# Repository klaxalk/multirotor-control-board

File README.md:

Multirotor Control Board
========================

Sources for the Multirotor Control Board developed at FEE CTU Prague by MRS Group. There are software and hardware sources located in this repository.

The control board is responsible for communication with modules and running basic controller for stabilization and surveilence.

------
### References
1. T. Baca, "_[Embedded Model Predictive Control of Unmanned Micro Aerial Vehicles](http://mrs.felk.cvut.cz/data/papers/DP_baca.pdf)_", 2015, Diploma Thesis, Czech Technical University in Prague.
2. T. Baca, G. Loianno and M. Saska, "_[Embedded Model Predictive Control of Unmanned Micro Aerial Vehicles](http://mrs.felk.cvut.cz/data/papers/mmar_2018_mpc.pdf)_". In 2016 21st International Conference on Methods and Models in Automation and Robotics (MMAR), 2016.
3. T. Baca, D. Hert, G. Loianno, M. Saska and V. Kumar, "_[Model Predictive Trajectory Tracking and Collision Avoidance for Reliable Outdoor Deployment of Unmanned Aerial Vehicles](http://mrs.felk.cvut.cz/data/papers/iros_2018_mpc.pdf)_". In IEEE International Conference on Intelligent Robots and Systems (IROS). 2018, 1-8.

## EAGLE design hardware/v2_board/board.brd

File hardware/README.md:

v1_board
--------

Eagle files for control board v1, January 2013.

v2_board
--------

Eagle files for control board v2, September 2014.

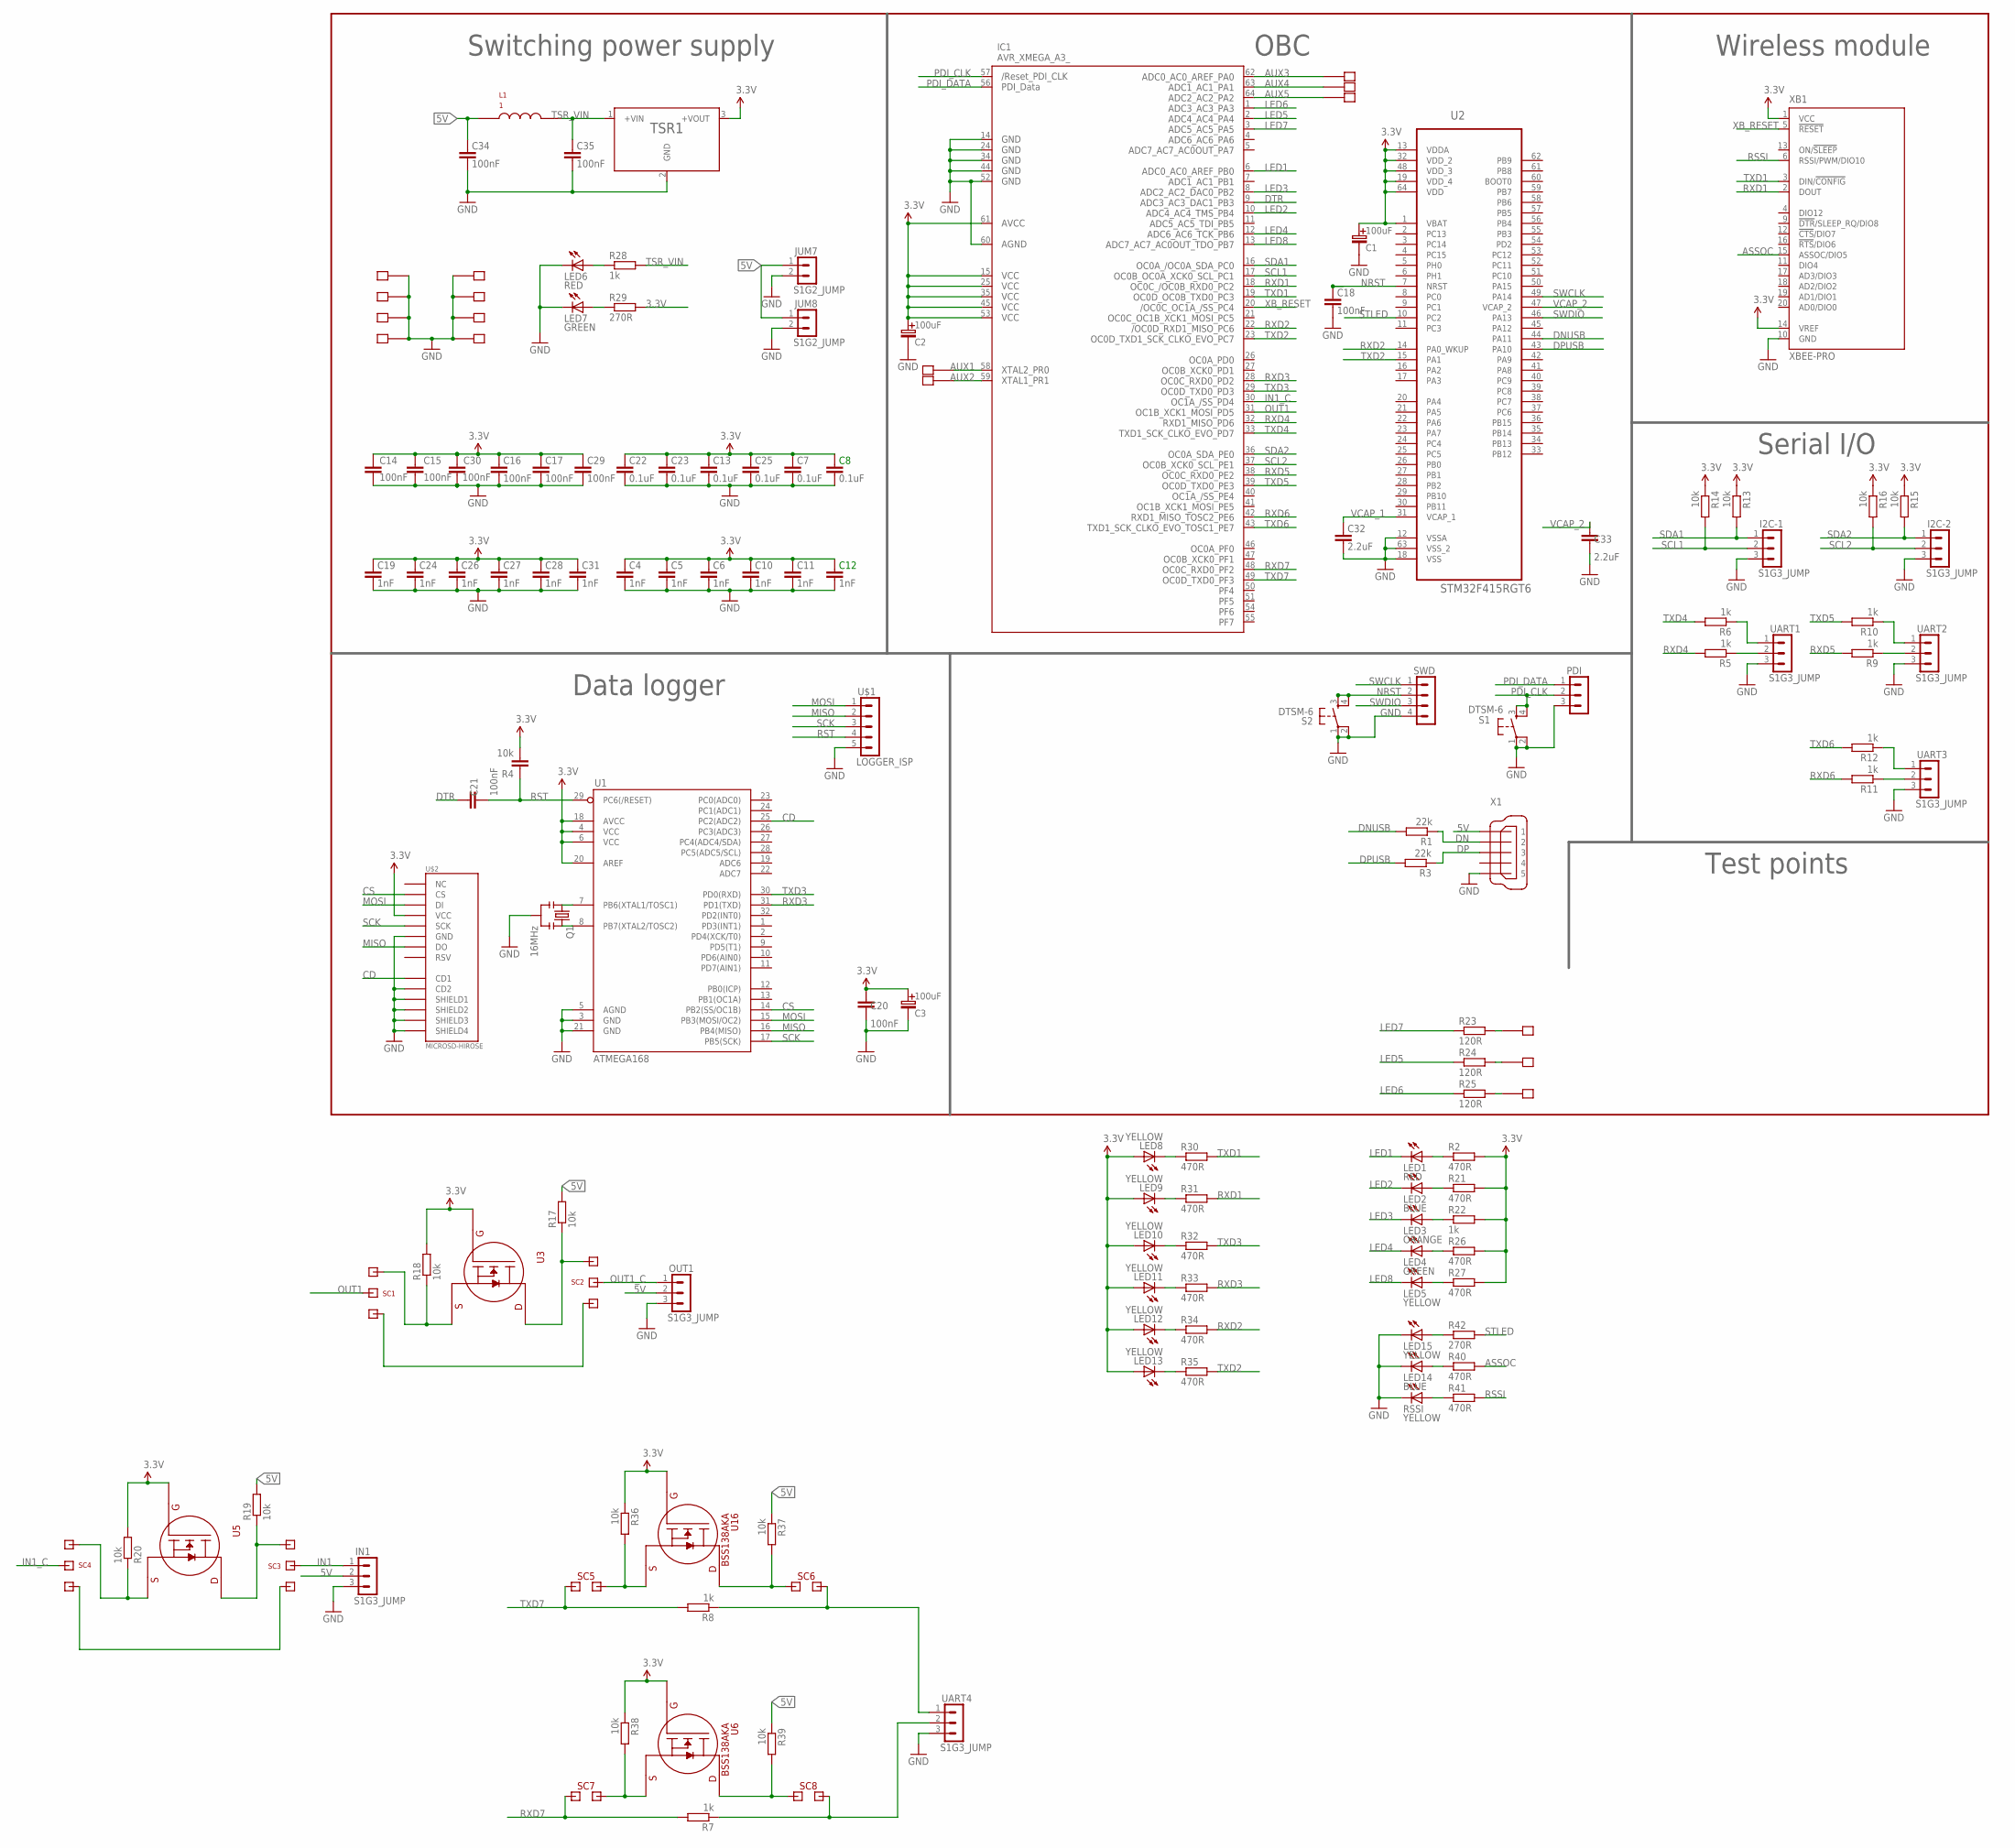
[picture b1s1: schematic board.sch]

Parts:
AUX1, AUX2, AUX3, AUX4, AUX5: PIN
C1, C2, C3: 100uF; B
C4, C5, C6, C10, C11, C12, C19, C24, C26, C27, C28, C31: 1nF; C0805
C7, C8, C13, C22, C23, C25: 0.1uF; C0805
C14, C15, C16, C17, C18, C20, C21, C29, C30, C34, C35: 100nF; C0805
C32, C33: 2.2uF; C0805
I2C-1, I2C-2: S1G3_JUMP; S1G3_JUM
IC1: AVR_XMEGA_A3_; TQFP64
IN1: S1G3_JUMP; S1G3_JUM
JUM7, JUM8: S1G2_JUMP; S1G2_JUM
L1: 1; SDR0604
LED1, LED6: RED; SML0805
LED2, LED14: BLUE; SML0805
LED3: ORANGE; SML0805
LED4, LED7: GREEN; SML0805
LED5, LED8, LED9, LED10, LED11, LED12, LED13, LED15: YELLOW; SML0805
OUT1: S1G3_JUMP; S1G3_JUM
PDI: S1G3_JUMP; S1G3_JUM
Q1: 16MHz; RESONATOR-SMD
R1, R3: 22k; R0805
R2, R21, R26, R27, R30, R31, R32, R33, R34, R35, R40, R41: 470R; R0805
R4: 10k; C0805
R5, R6, R7, R8, R9, R10, R11, R12, R22, R28: 1k; R0805
R13, R14, R15, R16, R17, R18, R19, R20, R36, R37, R38, R39: 10k; R0805
R23, R24, R25: 120R; R0805
R29, R42: 270R; R0805
RSSI: YELLOW; SML0805
S1, S2: DTSM-6
SC1, SC3: SOLDER_SWITCH_ONE; SOLDER_SWITCH
SC2, SC4: SOLDER_SWITCH_TWO; SOLDER_SWITCH
SC5, SC6, SC7, SC8: SOLDER_SWITCH_2
SWD: S1G4_JUMP_SQUARE; 2X02
TSR: TSR1
U1: ATMEGA168; TQFP32-08
U2: STM32F415RGT6; QFP50P1200X1200X160-64N
U3, U5, U6, U16: BSS138AKA; SOT-23
U$1: LOGGER_ISP
U$2: MICROSD-HIROSE; MICROSD_HOLDER-HIROSE-DM3AT
U$10, U$11, U$12, U$15, U$16, U$17, U$18, U$19, U$20, U$21, U$22: PIN
UART1, UART2, UART3, UART4: S1G3_JUMP; S1G3_JUM
X1: MINI-USB-UX60A-MB-5ST; UX60A-MB-5ST
XB1: XBEE-PRO

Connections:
3.3V: C1.+ (C_EL+), C2.+ (C_EL+), C3.+ (C_EL+), C4.2, C5.2, C6.2, C7.2, C8.2, C10.2, C11.2, C12.2, C13.2, C14.2, C15.2, C16.2, C17.2, C19.2, C20.2, C22.2, C23.2, C24.2, C25.2, C26.2, C27.2, C28.2, C29.2, C30.2, C31.2, IC1.15 (VCC1), IC1.25 (VCC2), IC1.35 (VCC3), IC1.45 (VCC4), IC1.53 (VCC5), IC1.61 (AVCC), LED8.A, LED9.A, LED10.A, LED11.A, LED12.A, LED13.A, R2.2, R4.2, R13.1, R14.1, R15.1, R16.1, R18.2, R20.2, R21.2, R22.2, R26.2, R27.2, R29.2, R36.1, R38.1, TSR.3 (+VOUT), U1.4 (VCC), U1.6 (VCC), U1.18 (AVCC), U1.20 (AREF), U2.1 (VBAT), U2.13 (VDDA), U2.19 (VDD_4), U2.32 (VDD_2), U2.48 (VDD_3), U2.64 (VDD), U3.1 (G), U5.1 (G), U6.1 (G), U16.1 (G), U$2.VDD (VCC), XB1.1 (VCC), XB1.14 (VREF)
5V: C34.2, IN1.2, JUM7.1, JUM8.1, L1.P$1, OUT1.2, R17.2, R19.2, R37.1, R39.1, X1.1
ASSOC: R40.2, XB1.15 (ASSOC/DIO5)
AUX1: AUX1.P$1, IC1.58 (PR0)
AUX2: AUX2.P$1, IC1.59 (PR1)
AUX3: AUX3.P$1, IC1.62 (PA0)
AUX4: AUX4.P$1, IC1.63 (PA1)
AUX5: AUX5.P$1, IC1.64 (PA2)
CD: U1.25 (PC2(ADC2)), U$2.CD1
CS: U1.14 (PB2(SS/OC1B)), U$2.DAT3 (CS)
DN: R1.1, X1.2
DNUSB: R1.2, U2.44 (PA11)
DP: R3.1, X1.3
DPUSB: R3.2, U2.43 (PA10)
DTR: C21.2, IC1.9 (PB3)
GND: C1.- (C_EL-), C2.- (C_EL-), C3.- (C_EL-), C4.1, C5.1, C6.1, C7.1, C8.1, C10.1, C11.1, C12.1, C13.1, C14.1, C15.1, C16.1, C17.1, C18.1, C19.1, C20.1, C22.1, C23.1, C24.1, C25.1, C26.1, C27.1, C28.1, C29.1, C30.1, C31.1, C32.1, C33.1, C34.1, C35.1, I2C-1.3, I2C-2.3, IC1.14 (GND1), IC1.24 (GND2), IC1.34 (GND3), IC1.44 (GND4), IC1.52 (GND5), IC1.60 (AGND), IN1.3, JUM7.2, JUM8.2, LED6.C, LED7.C, LED14.C, LED15.C, OUT1.3, PDI.3, Q1.2, RSSI.C, S1.1, S1.2, S2.1, S2.2, SWD.4, TSR.2 (GND), U1.3 (GND), U1.5 (AGND), U1.21 (GND), U2.12 (VSSA), U2.18 (VSS), U2.63 (VSS_2), U$1.5, U$2.BODY1 (SHIELD1), U$2.BODY2 (SHIELD2), U$2.BODY3 (SHIELD3), U$2.BODY4 (SHIELD4), U$2.CD2, U$2.VSS (GND), U$15.P$1, U$16.P$1, U$17.P$1, U$18.P$1, U$19.P$1, U$20.P$1, U$21.P$1, U$22.P$1, UART1.3, UART2.3, UART3.3, UART4.3, X1.5, XB1.10 (GND)
IN1: IN1.1, SC3.MID
IN1_C: IC1.30 (PD4), SC4.MID
LED1: IC1.6 (PB0), LED1.C
LED2: IC1.10 (PB4), LED2.C
LED3: IC1.8 (PB2), LED3.C
LED4: IC1.12 (PB6), LED4.C
LED5: IC1.2 (PA4), R24.1
LED6: IC1.1 (PA3), R25.1
LED7: IC1.3 (PA5), R23.1
LED8: IC1.13 (PB7), LED5.C
MISO: U1.16 (PB4(MISO)), U$1.2, U$2.DAT0 (DO)
MOSI: U1.15 (PB3(MOSI/OC2)), U$1.1, U$2.CMD (DI)
unnamed: Q1.3, U1.8 (PB7(XTAL2/TOSC2))
unnamed: Q1.1, U1.7 (PB6(XTAL1/TOSC1))
unnamed: LED1.A, R2.1
unnamed: R25.2, U$12.P$1
unnamed: R5.1, UART1.2
unnamed: R6.1, UART1.1
unnamed: LED3.A, R22.1
unnamed: R17.1, SC2.1 (2), U3.3 (D)
unnamed: R18.1, SC1.1, U3.2 (S)
unnamed: R10.1, UART2.1
unnamed: R9.1, UART2.2
unnamed: R12.1, UART3.1
unnamed: R11.1, UART3.2
unnamed: LED8.C, R30.1
unnamed: R20.1, SC4.1 (2), U5.2 (S)
unnamed: R36.2, SC5.1, U16.2 (S)
unnamed: LED6.A, R28.1
unnamed: LED2.A, R21.1
unnamed: LED7.A, R29.1
unnamed: LED4.A, R26.1
unnamed: LED9.C, R31.1
unnamed: R38.2, SC7.1, U6.2 (S)
unnamed: R37.2, SC6.MID, U16.3 (D)
unnamed: LED10.C, R32.1
unnamed: R39.2, SC8.MID, U6.3 (D)
unnamed: LED11.C, R33.1
unnamed: LED12.C, R34.1
unnamed: LED13.C, R35.1
unnamed: LED5.A, R27.1
unnamed: R19.1, SC3.1, U5.3 (D)
unnamed: SC3.2, SC4.2 (1)
unnamed: R23.2, U$10.P$1
unnamed: LED14.A, R40.1
unnamed: SC1.2, SC2.2 (1)
unnamed: R41.1, RSSI.A
unnamed: R24.2, U$11.P$1
unnamed: LED15.A, R42.1
NRST: C18.2, S2.3, S2.4, SWD.2, U2.7 (NRST)
OUT1: IC1.31 (PD5), SC1.MID
OUT1_C: OUT1.1, SC2.MID
PDI_CLK: IC1.57 (RESET), PDI.2, S1.3, S1.4
PDI_DATA: IC1.56 (PDI_DATA), PDI.1
RSSI: R41.2, XB1.6 (RSSI/PWM/DIO10)
RST: C21.1, R4.1, U1.29 (PC6(/RESET)), U$1.4
RXD1: IC1.18 (PC2), R31.2, XB1.2 (DOUT)
RXD2: IC1.22 (PC6), R34.2, U2.14 (PA0_WKUP)
RXD3: IC1.28 (PD2), R33.2, U1.31 (PD1(TXD))
RXD4: IC1.32 (PD6), R5.2
RXD5: IC1.38 (PE2), R9.2
RXD6: IC1.42 (PE6), R11.2
RXD7: IC1.48 (PF2), R7.2, SC7.MID
RXD77: R7.1, SC8.1, UART4.2
SCK: U1.17 (PB5(SCK)), U$1.3, U$2.CLK (SCK)
SCL1: I2C-1.2, IC1.17 (PC1), R14.2
SCL2: I2C-2.2, IC1.37 (PE1), R16.2
SDA1: I2C-1.1, IC1.16 (PC0), R13.2
SDA2: I2C-2.1, IC1.36 (PE0), R15.2
STLED: R42.2, U2.10 (PC2)
SWCLK: SWD.1, U2.49 (PA14)
SWDIO: SWD.3, U2.46 (PA13)
TSR_VIN: C35.2, L1.P$2, R28.2, TSR.1 (+VIN)
TXD1: IC1.19 (PC3), R30.2, XB1.3 (DIN/!CONFIG)
TXD2: IC1.23 (PC7), R35.2, U2.15 (PA1)
TXD3: IC1.29 (PD3), R32.2, U1.30 (PD0(RXD))
TXD4: IC1.33 (PD7), R6.2
TXD5: IC1.39 (PE3), R10.2
TXD6: IC1.43 (PE7), R12.2
TXD7: IC1.49 (PF3), R8.2, SC5.MID
TXD77: R8.1, SC6.1, UART4.1
VCAP_1: C32.2, U2.31 (VCAP_1)
VCAP_2: C33.2, U2.47 (VCAP_2)
XB_RESET: IC1.20 (PC4), XB1.5 (!RESET)

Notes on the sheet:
Switching power supply
OBC
Wireless module
Serial I/O
Data logger
Test points

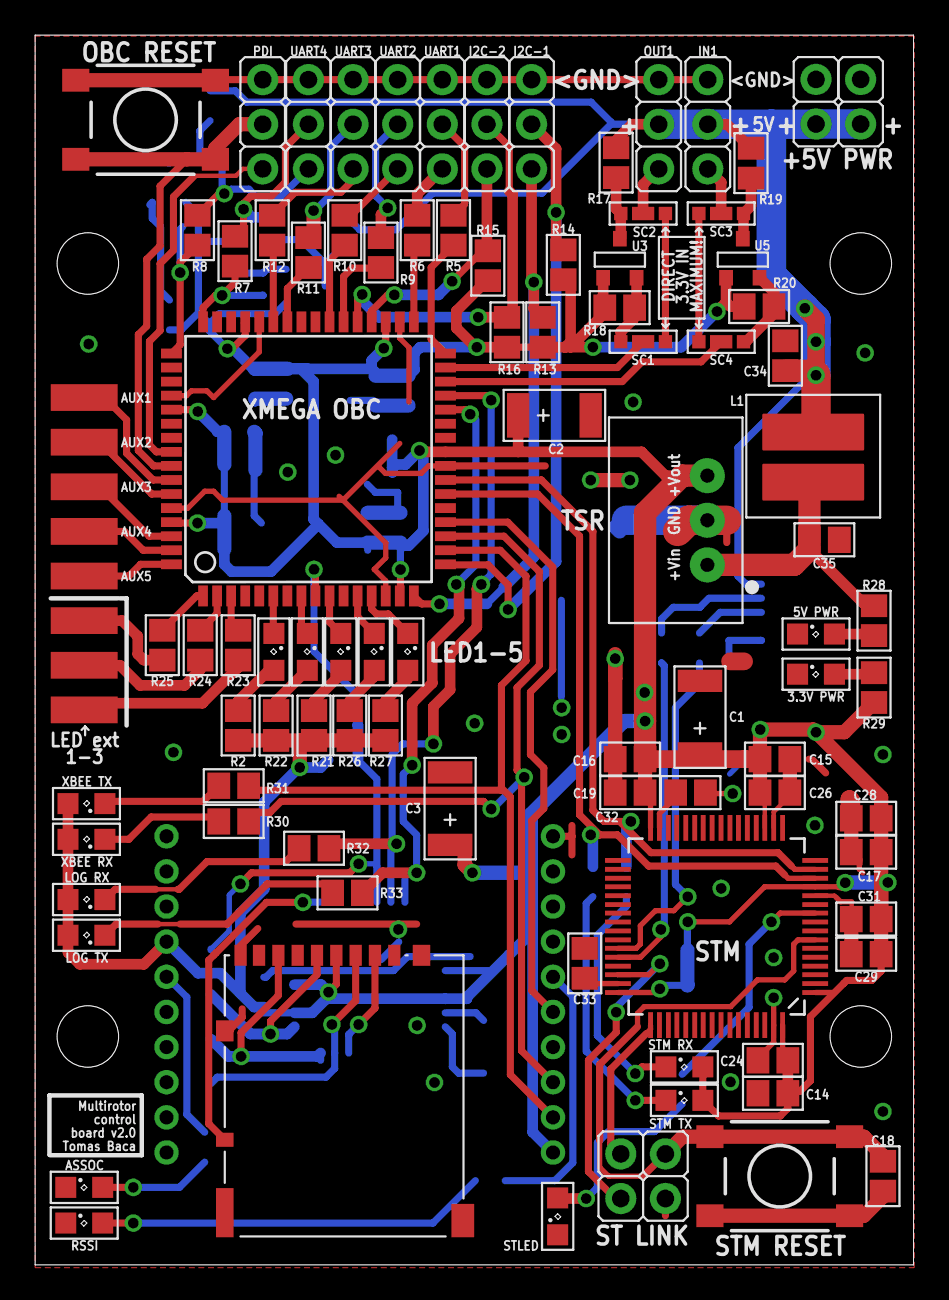
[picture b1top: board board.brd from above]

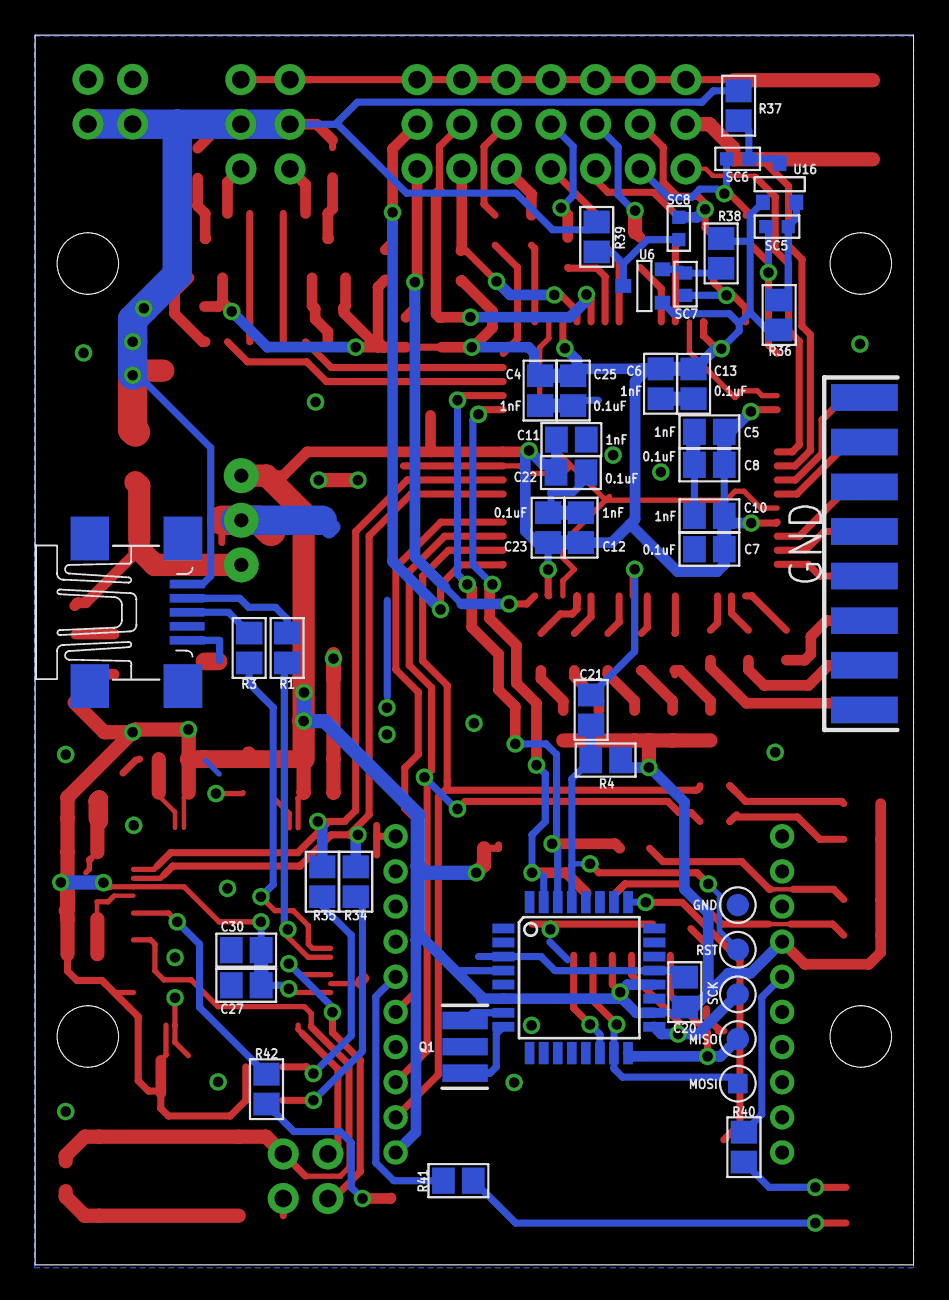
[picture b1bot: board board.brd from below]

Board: 2 copper layers, 50.0 x 70.0 mm, 144 parts (46 on the bottom side), 100 nets.

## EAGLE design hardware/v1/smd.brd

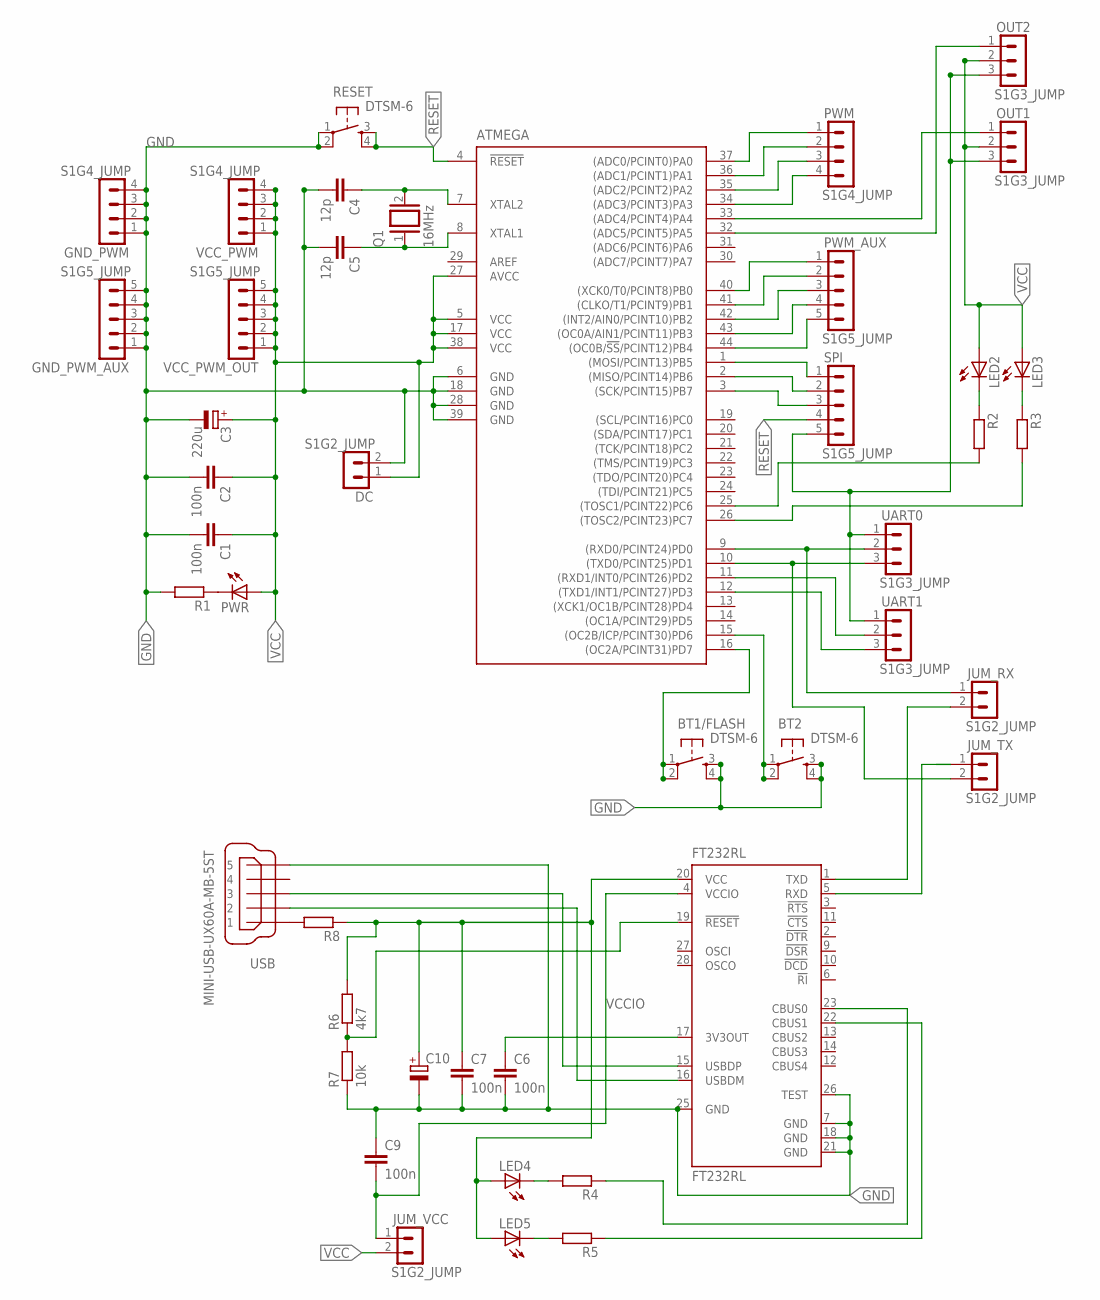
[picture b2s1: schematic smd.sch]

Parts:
ATMEGA: MEGA164P/324P/644P-AU; TQFP44
BT1/FLASH, BT2: DTSM-6
C1, C2, C6, C7, C9: 100n; C0805
C3: 220u; 150CLZ-0810
C4, C5: 12p; C0805
C10: CPOL-EUSMCD; SMC_D
DC: S1G2_JUMP; S1G2_JUM
FT232RL: FT232RL; SSOP28
GND_PWM: S1G4_JUMP; S1G4_JUM
GND_PWM_AUX: S1G5_JUMP; S1G5_JUM
JUM_RX: S1G2_JUMP; S1G2_JUM
JUM_TX: S1G2_JUMP; S1G2_JUM
JUM_VCC: S1G2_JUMP; S1G2_JUM
LED2, LED3, LED4, LED5: LEDSML0805; SML0805
OUT1, OUT2: S1G3_JUMP; S1G3_JUM
PWM: S1G4_JUMP; S1G4_JUM
PWM_AUX: S1G5_JUMP; S1G5_JUM
PWR: LEDSML0805; SML0805
Q1: 16MHz; QS
R1, R2, R3, R4, R5, R8: R-EU_R0805; R0805
R6: 4k7; R0805
R7: 10k; R0805
RESET: DTSM-6
SPI: S1G5_JUMP; S1G5_JUM
UART0, UART1: S1G3_JUMP; S1G3_JUM
USB: MINI-USB-UX60A-MB-5ST; UX60A-MB-5ST
VCC_PWM: S1G4_JUMP; S1G4_JUM
VCC_PWM_OUT: S1G5_JUMP; S1G5_JUM

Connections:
AREF: ATMEGA.29 (AREF)
ATMEGA_RX0: ATMEGA.9 ((RXD0/PCINT24)PD0), JUM_RX.1, UART0.2
ATMEGA_RX1: ATMEGA.11 ((RXD1/INT0/PCINT26)PD2), UART1.2
ATMEGA_TX0: ATMEGA.10 ((TXD0/PCINT25)PD1), JUM_TX.2, UART0.3
ATMEGA_TX1: ATMEGA.12 ((TXD1/INT1/PCINT27)PD3), UART1.3
FT_RX: FT232RL.5 (RXD), JUM_TX.1
FT_TX: FT232RL.1 (TXD), JUM_RX.2
GND: ATMEGA.6 (GND), ATMEGA.18 (GND), ATMEGA.28 (GND), ATMEGA.39 (GND), BT1/FLASH.3, BT1/FLASH.4, BT2.3, BT2.4, C1.2, C2.2, C3.-, C4.2, C5.2, C6.2, C7.2, C9.1, C10.-, DC.2, FT232RL.7 (GND), FT232RL.18 (GND), FT232RL.21 (GND), FT232RL.25 (GND), FT232RL.26 (TEST), GND_PWM.1, GND_PWM.2, GND_PWM.3, GND_PWM.4, GND_PWM_AUX.1, GND_PWM_AUX.2, GND_PWM_AUX.3, GND_PWM_AUX.4, GND_PWM_AUX.5, OUT1.3, OUT2.3, R1.2, R7.1, RESET.1, RESET.2, SPI.5, UART0.1, UART1.1, USB.5
MISO: ATMEGA.2 ((MISO/PCINT14)PB6), SPI.2
MOSI: ATMEGA.1 ((MOSI/PCINT13)PB5), SPI.1
unnamed: ATMEGA.37 ((ADC0/PCINT0)PA0), PWM.1
unnamed: ATMEGA.36 ((ADC1/PCINT1)PA1), PWM.2
unnamed: ATMEGA.7 (XTAL2), C4.1, Q1.2
unnamed: ATMEGA.8 (XTAL1), C5.1, Q1.1
unnamed: LED2.C, R2.1
unnamed: ATMEGA.35 ((ADC2/PCINT2)PA2), PWM.3
unnamed: ATMEGA.34 ((ADC3/PCINT3)PA3), PWM.4
unnamed: ATMEGA.40 ((XCK0/T0/PCINT8)PB0), PWM_AUX.1
unnamed: ATMEGA.41 ((CLKO/T1/PCINT9)PB1), PWM_AUX.2
unnamed: ATMEGA.42 ((INT2/AIN0/PCINT10)PB2), PWM_AUX.3
unnamed: ATMEGA.43 ((OC0A/AIN1/PCINT11)PB3), PWM_AUX.4
unnamed: ATMEGA.44 ((OC0B/!SS!/PCINT12)PB4), PWM_AUX.5
unnamed: FT232RL.19 (!RESET), R6.1, R7.2
unnamed: LED4.C, R4.2
unnamed: LED5.C, R5.2
unnamed: FT232RL.23 (CBUS0), R4.1
unnamed: PWR.C, R1.1
unnamed: LED3.C, R3.1
unnamed: ATMEGA.15 ((OC2B/ICP/PCINT30)PD6), BT2.1, BT2.2
unnamed: R8.2, USB.1
unnamed: ATMEGA.26 ((TOSC2/PCINT23)PC7), R3.2
unnamed: ATMEGA.25 ((TOSC1/PCINT22)PC6), R2.2
unnamed: FT232RL.22 (CBUS1), R5.1
unnamed: ATMEGA.33 ((ADC4/PCINT4)PA4), OUT1.1
unnamed: ATMEGA.16 ((OC2A/PCINT31)PD7), BT1/FLASH.1, BT1/FLASH.2
unnamed: ATMEGA.32 ((ADC5/PCINT5)PA5), OUT2.1
unnamed: C6.1, FT232RL.17 (3V3OUT)
RESET: ATMEGA.4 (!RESET), RESET.3, RESET.4, SPI.4
SCK: ATMEGA.3 ((SCK/PCINT15)PB7), SPI.3
USBDM: FT232RL.16 (USBDM), USB.2
USBDP: FT232RL.15 (USBDP), USB.3
VCC: ATMEGA.5 (VCC), ATMEGA.17 (VCC), ATMEGA.27 (AVCC), ATMEGA.38 (VCC), C1.1, C2.1, C3.+, DC.1, JUM_VCC.2, LED2.A, LED3.A, OUT1.2, OUT2.2, PWR.A, VCC_PWM.1, VCC_PWM.2, VCC_PWM.3, VCC_PWM.4, VCC_PWM_OUT.1, VCC_PWM_OUT.2, VCC_PWM_OUT.3, VCC_PWM_OUT.4, VCC_PWM_OUT.5
VCCIO: C9.2, FT232RL.4 (VCCIO), JUM_VCC.1
VCC_USB: C7.1, C10.+, FT232RL.20 (VCC), LED4.A, LED5.A, R6.2, R8.1

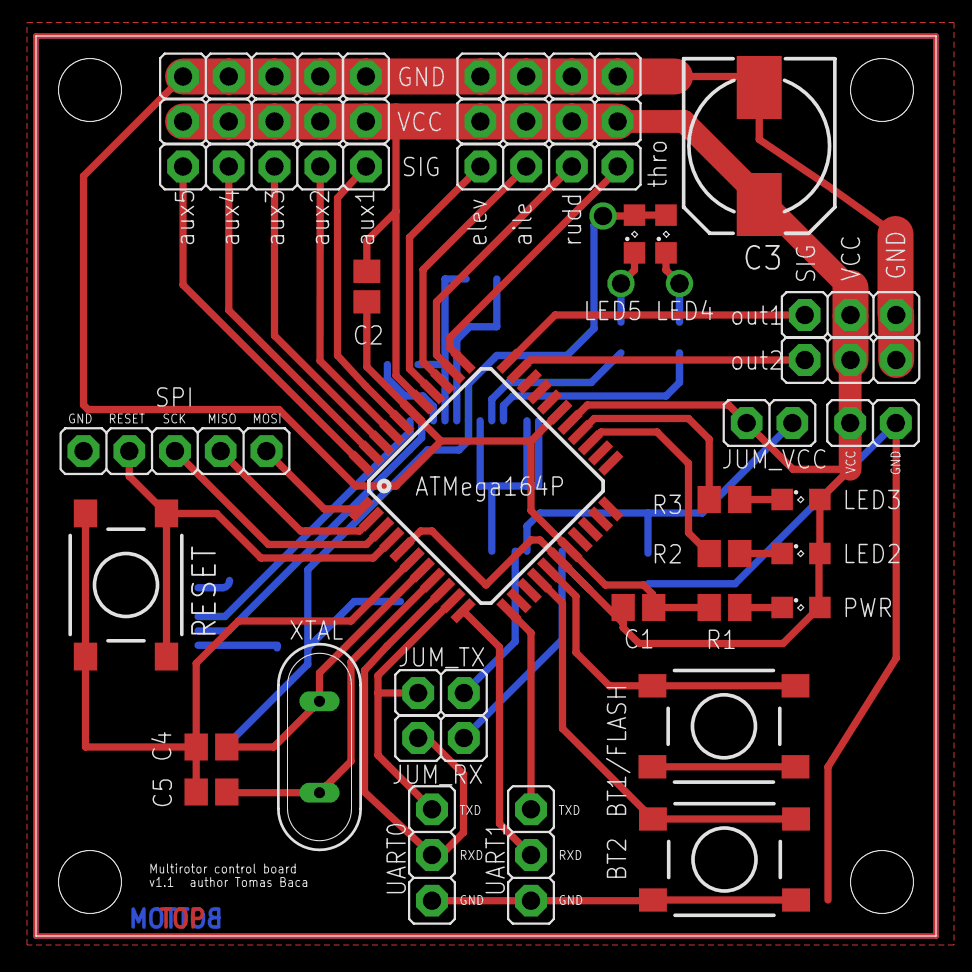
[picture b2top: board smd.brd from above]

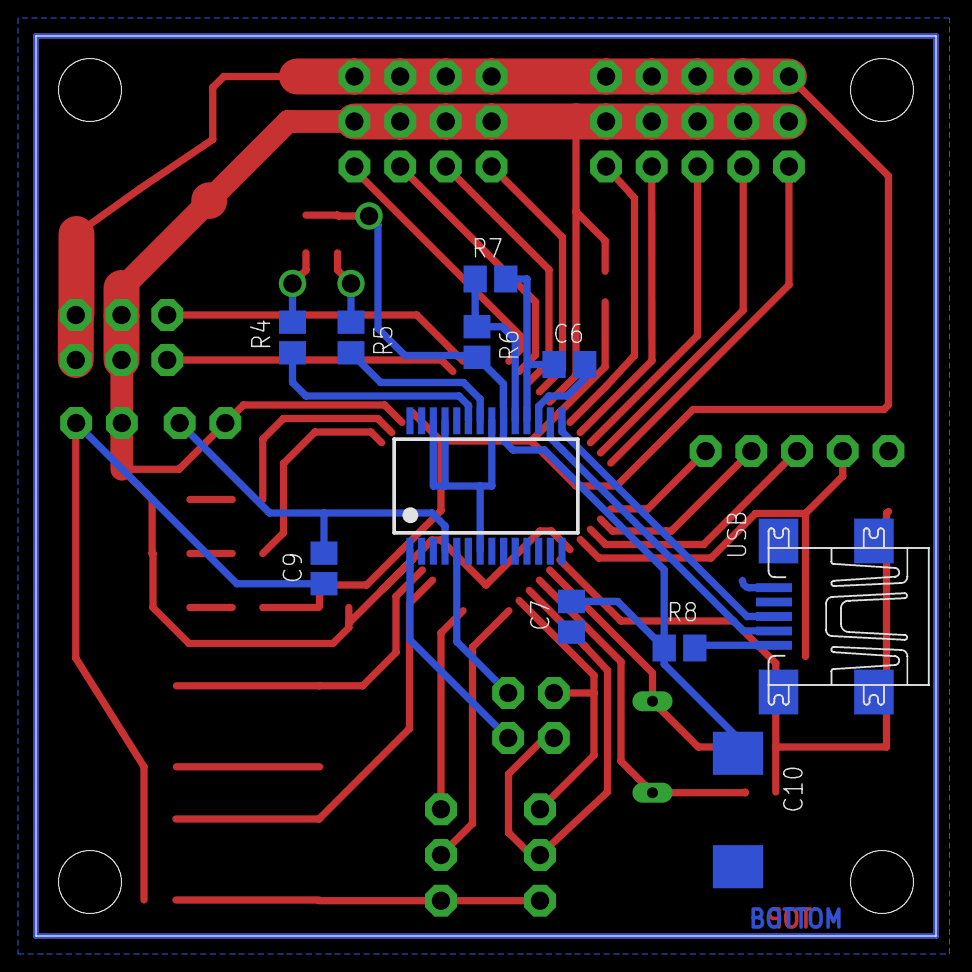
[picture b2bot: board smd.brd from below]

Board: 2 copper layers, 50.0 x 50.0 mm, 44 parts (11 on the bottom side), 43 nets.

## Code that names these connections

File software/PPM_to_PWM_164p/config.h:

/*
 * The configuration file for the main project
 */

#ifndef _CONFIG_H
#define _CONFIG_H

//~ --------------------------------------------------------------------
//~ PWM and PPM constants values configuration
//~ --------------------------------------------------------------------

// PWM constants
#define PULSE_MIN 2304		// PWM
#define PULSE_MAX 4608		// PWM
#define PULSE_MIDDLE 3456	// PWM
#define PPM_PULSE 461		// PWM
#define PPM_FRAME_LENGTH 46080	// PWM and PPM

#define	PULSE_OUT_MIN	1152
#define	PULSE_OUT_MIDDLE	1728

// Constants for 16 Mhz
/*
 * #define pulseMin 2000 		// PWM
 * #define pulseMax 4000 		// PWM
 * #define pulseMiddle 3000 	// PWM
 * #define ppmPulse 800 		// PPM
 * #define frameLength 40000 	// PWM and PPM
 */

// Constants for internal 8 Mhz
/*
 * #define pulseMin 1000
 * #define pulseMax 2000
 * #define pulseMiddle 1500
 * #define ppmPulse 400
 * #define frameLength 20000
 */

//~ --------------------------------------------------------------------
//~ RC channels configuration
//~ --------------------------------------------------------------------

// define RC channel order in
#define ELEVATOR 0		//PA0
#define AILERON 1		//PA1
#define RUDDER 2		//PA2
#define THROTTLE 3		//PA3

#define AUX1 4			//PB0
#define AUX2 5			//PB1
#define AUX3 6			//PB2
#define AUX4 7			//PB3
#define AUX5 8			//PB4

//~ --------------------------------------------------------------------
//~ Basic macros configuration
//~ --------------------------------------------------------------------

// define basic macros
#define led_R_on()  PORTC &= ~_BV(7)
#define led_R_off()  PORTC  |= _BV(7)
#define led_Y_on()  PORTC &= ~_BV(6)
#define led_Y_off()  PORTC |= _BV(6)
#define led_R_toggle() PORTC ^= _BV(7)
#define led_Y_toggle() PORTC ^= _BV(6)
#define led_control_on() PORTA |= _BV(5)
#define led_control_off() PORTA &= ~_BV(5)
#define led_control_toggle() PORTA ^= _BV(5)
#define pulse1_on()  PORTA |= _BV(4) // set output1 to 1
#define pulse1_off()  PORTA &= ~_BV(4) // set output1 to 0

#endif // _CONFIG_H

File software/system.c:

/*
 * This file contains functions for control and configuration of the system
 */

#include "system.h"

// disable controllers
void disableController() {

	controllerEnabled = 0;
}

// enable controllers
void enableController() {

	if (controllerEnabled == 0) {

#if PX4FLOW_DATA_RECEIVE == ENABLED

		elevatorIntegration = 0;
		aileronIntegration = 0;
		throttleIntegration = 0;

#endif
	}
	controllerEnabled = 1;
}

void disablePositionController() {

	positionControllerEnabled = 0;
}

void enablePositionController() {

	if (positionControllerEnabled == 0) {
		// set integrated variables to default
	}
	positionControllerEnabled = 1;
}

// set the parameters of the MCU
void initializeMCU() {

	// stop all interrupts
	cli();

	// set port PC6 as green LED and PC7 as red LED
	DDRC |= _BV(PC6)|_BV(PC7);

	// set port PA4 as output1 (PPM) and PA5 as output2
	DDRA |= _BV(PA4)|_BV(PA5);

	// set ports PA0 .. PA7 as inputs (channels)
	DDRA |= 0b11110000;

	// set ports PB0 .. PB4 as aux inputs
	DDRB |= 0b11100000;

	// button1 pullup
	PORTD |= (1<<PD7);

	// button2 pullup
	PORTD |= (1<<PD6);

	// set pull ups for ports PA0 .. PA7
	PORTA |= 0b11110000;

	// set pull ups for ports PB0 .. PB4
	PORTB |= 0b11100000;

	// enables 16timer
	TIMSK1 |= _BV(OCIE1A)|_BV(OCIE1B);

	// using /8 prescaler
	TCCR1B |= _BV(CS11);

	// enables 8timer
	TIMSK0 |= _BV(TOIE0);

	// using /1024 prescaler
	TCCR0B |= _BV(CS02)|_BV(CS00);

	// external interrupts
	// any change of PCINT0 - PCINT7 will fire interrupt
	EICRA |= _BV(ISC00);

	// any change of PCINT8 - PCINT15 will fire interrupt
	EICRA |= _BV(ISC10);

	// enable pin change interrupt on ports PCINT0 - PCINT7 (PA0 .. PA7)
	PCICR |= _BV(PCIE0);

	// enable pin change interrupt on ports PCINT8 - PCINT15 (PB0 - PB7)
	PCICR |= _BV(PCIE1);

	// enables pin change interrupt flag for PCINT0 - PCINT7
	PCIFR |= _BV(PCIF0);

	// enables pin change interrupt flag for PCINT8 - PCINT15
	PCIFR |= _BV(PCIF1);

	// trigger on change of PCINT1 pins PA0 .. PA7
	PCMSK0 |= 0b00001111;

	// mask for PB
	PCMSK1 |= 0b00011111;

	// copy actual PINA states into portMask
	portMask = PINA;

	// copy actual PINA states into portMask
	portMask2 = PINB;

	// serial init 0
	USART0_init(MYUBRR0);

	// serial init 1
	USART1_init(MYUBRR1);

	led_R_off();
	led_Y_off();
	led_control_off();

	// turn all interupts on
	sei();
}

#if ATOM_DATA_RECEIVE == ENABLED

// functions for pitch buffer

uint8_t bufferSucc(uint8_t ptr, const uint8_t size) {
	ptr++;
	if (ptr==size) {
		ptr=0;
	}
	return ptr;
}

uint8_t pitchBufferEmpty() {

	return (pitchBufferFirst == pitchBufferLast);
}

void pitchBufferPut(int16_t c) {
	uint8_t last = bufferSucc(pitchBufferLast, PITCH_BUFFER_SIZE);
	if (last == pitchBufferFirst) {
		return;
	}
	pitchBuffer[last] = c;
	pitchBufferNum++;
	pitchBufferLast = last;
}

int16_t pitchBufferGet() {
	if (pitchBufferEmpty()) {
		return 0;
	}
	uint8_t first = bufferSucc(pitchBufferFirst, PITCH_BUFFER_SIZE);
	int16_t result = pitchBuffer[first];
	pitchBufferFirst = first;
	pitchBufferNum--;
	return result;
}

uint8_t rollBufferEmpty() {

	return (rollBufferFirst == rollBufferLast);
}

void rollBufferPut(int16_t c) {
	uint8_t last = bufferSucc(rollBufferLast, ROLL_BUFFER_SIZE);
	if (last == rollBufferFirst) {
		return;
	}
	rollBuffer[last] = c;
	rollBufferNum++;
	rollBufferLast = last;
}

int16_t rollBufferGet() {
	if (rollBufferEmpty()) {
		return 0;
	}
	uint8_t first = bufferSucc(rollBufferFirst, ROLL_BUFFER_SIZE);
	int16_t result = rollBuffer[first];
	rollBufferFirst = first;
	rollBufferNum--;
	return result;
}

#endif

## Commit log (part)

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2013-09-19 Funguje regulator s gumstixem.
2013-09-20 Naladěné sledování blobu se studentským letounem.
2013-09-22 Vytvořena podsložka "software" a do ní vše přesunuto.
2013-09-22 Teď už opravdu přesunuto.
2013-09-22 Úpravy v podmínkách preprocesoru, korektnější oddělení kódu pro moduly.
2013-09-23 Oprava drobností
2013-09-23 Nové logování se surfnavem
2013-09-25 Úpravy na studentské dróně. Regulátor funguje uspokojivě.
2013-10-04 Korekce dat ze surfu, zavedení úuhlové zpětné vazby do stabilizace se surfem.
2013-10-04 Obrázky k manuálu.
2013-10-09 Drobne zmeny
2013-10-09 Oprava chyby v controllers.c
2013-10-13 Aktualizace návodu - logování dat, předletová příprava, Gumstix.
2013-11-28 Bug fix posilani kanalu AUX3 az AUX5 z RC
2013-12-05 Odebrány konstanty z nastavení regulátorů
2013-12-06 Matlab funkce na čištění dat + gitignore
2013-12-18 minor changes
2014-01-21 Manuál - oprava gest pro kalibraci.
2014-02-04 debug updated, PX4Flow data led repaired
2014-03-27 controllers rework
2014-04-01 bugfixes
2014-04-01 removed unused code
2014-04-08 final position controller
2014-04-09 trajectory following
2014-04-09 landing automat
2014-04-09 optimalization - trajectory in int16
2014-04-09 optimalization - debug floats
2014-04-16 fixes
2014-04-18 more fixes
2014-06-24 Camera rotated to Landscape, trajectory and setpoints modified
2014-06-25 New trajectories for experiments
2014-06-25 + Gumstix software + Corrected manual, correct calibration pictures
2014-09-03 + Software V2
2014-09-04 + ARM software
    + updated xmega uart driver
2014-09-04 Fixed uart interrupt in ArmMCU
2014-09-06 gitignore update
2014-09-09 New firmware for PPM_to_PWM board
    New firmware for ATMega164p (v1_board) wich converts the PWM from RC
    receiver to PPM with 1/2 of standard PPM pulse lenghts.
2014-09-09 + RC simulator setup manual
    * directories structure modified
2014-09-10 + system.c with MCU initialization
2014-09-10 + much readme, so information
2014-09-11 + mainTask and commTask
2014-09-11 + px4flow support
2014-09-11 + PX4Flow telemetry
2014-09-13 + Ready to fly with the Tricopter
2014-09-14 Tricopter update
2014-09-17 + Just works
    + Altitude estimator repaired (fabs)
    + mavlink_parse_char used instead of my_mavlink_parse_char
    + baudrate for px4flow set to match the px4flow baudrate
2014-09-27 packets functions
    +create packet head
    +decompose packets
    +serial line packet communication
2014-09-27 + Telemetry response
    +commands
    +packet response
2014-10-09 Branching commit
2014-10-16 comm with openLog
2014-10-22 xbee
2014-10-23 Fixed default RC channel values
2014-10-23 added some TODOs
2014-10-23 Removed fiedlji2's files
2014-10-26 Add commands and packet files
2014-10-26 Packets transmitting works
2014-10-26 Landing + Trajectory ON/OFF
2014-10-26 Controllers ON/OFF
2014-10-28 + Trajectory point add
2014-10-28 Communication (.c .h) refactor
    variables moved to controllers.c
    flight ctrl comm. deleted
2014-10-28 CommTask.c refactor
2014-10-29 debug
2014-10-29 +UART 3 Bluetooth
2014-10-29 Controllers (.c .h) externs refactor
2014-10-29 -Bluetooth + config.h refactor II
2014-10-29 it works
2014-10-29 Switch controllers mapping + default setpoints
2014-10-30 Split Velocity and Position Controllers
    + add velocity setpoint
2014-10-30 +Telemetry +Velocity controller in controllersTask
    +Throttle speed
    +Ground distance estimated
    +Controllers outputs
2014-10-30 +Velocity setpoints update
    +XBee support
    +Saturation
    +Controller status TUI
2014-10-31 Code simplification, extern fixed
    + Fixed code duplicates
2014-10-31 +Gumstix ON/OFF, speedSedpoints Null
    +ONOFF type
    +XBee FrameID 0x00
    +speedSetpoints bugfix
2014-10-31 Both controllers on, Gumstix on bugfix
2014-10-31 + OpenLog support
2014-10-31 Trajectory follow change
    New method for setting setpoints
    Trajectory follow only if gumstix is not enabled
2014-10-31 Gumstix safety land
2014-11-03 -reports after change +K1 altitude lead
    +landing bugfix
2014-11-04 + Osazovací výkresy
2014-11-04 + scheme polished & schema png
2014-11-04 commited missing changes from previous removed unnecessary data files from this branch
2014-11-05 + OpenLog
    PWM_to_PPM corrected default PPM values
2014-11-05 K2 add
2014-11-05 Saturation + landing buggfix
2014-11-05 upload traj change
2014-11-06 + PPM_to_PWM defaults corrected
2014-11-07 implemented debugging over uart re-written RC switch reading
2014-11-07 K3 add
2014-11-09 smoother landing
2014-11-10 openLog,funkcni bez xbee
2014-11-11 funkcni bez xbee
2014-11-11 XBee 19200baud, landing status remake
2014-11-11 Telemetry To Coordinator Array + Commands
2014-11-13 +XBee start delay; second velocity filter
2014-11-14 +xbee
2014-11-14 uprava pameti tasku a RTOS
2014-11-16 + Kalman filter
2014-11-18 added setup_dirs.sh
2014-11-19 velocity controler remake
2014-11-20 +Report to Coordinator, more telemetry
2014-11-20 more coor reports
2014-11-20 message bugfix
2014-11-20 cont pos vel des
2014-11-21 Revert "cont pos vel des"
    This reverts commit 46c2a046090de33538a4249f5bc084729edc404e.
2014-11-21 change
2014-11-21 vetsi rozptyl pro packy
    samovzletavani kvadro je dano zmenami v signalu packy na vysilacce
2014-11-22 MPC is coming #2
2014-11-23 MPC is coming #3
2014-11-24 Implementing matrix library
2014-11-27 + Matrix multiplication etc..
    + non-equidistant action is optimized
2014-11-27 + pgmspace
2014-11-27 +Leading data remake
    Leading data in single payload
    Leading data TTL add, speed 0 if dead
2014-11-30 default values in mergeSignalsToOutput
2014-11-30 implementing kalman
2014-12-05 debug
    lead data
    landing
    no pos drifting when low
2014-12-08 + missing copy to output
2014-12-09 Kalman iteration complete
    + some minor functions to matrixLib
2014-12-10 bug fixes
    matrix inversion works
2014-12-10 kalman almost working, still buggy
2014-12-11 Packet trajectory , controllers change
2014-12-12 Kalman is working
    + RTC
2014-12-13 leader data Error
2014-12-17 follower set 01
2014-12-18 Status automatic report
2014-12-18 XBee desktop knihovna update
2015-01-08 jirkuv kod
2015-01-09 funkcni
2015-01-09 + config for openLog
2015-01-11 +GUI log
2015-01-16 trajectory+debug
    trajectory index overwrite
2015-01-17 Kalman moved to ARM
    + matrixLib moved to its own repository
2015-01-17 updated CMatrixLib
2015-01-18 Kalman working on ARM
    + Fixed tidious bug with task priorities
2015-01-18 USART on AMR rewritten to interrupts
2015-01-19 Kalman working on both axies
2015-01-19 + MPC matrices
2015-01-20 first MPC routine
2015-01-20 MPC's outputs present in xMega
2015-01-20 Added H_inv matrix for P=0.03
2015-01-20 MPC on tricopter #1
    + Data seems right
2015-01-22 Data logging via XBEE
2015-01-22 Model identification of Mikrokopter
2015-01-26 Gumstix solo position
2015-01-26 -gumstix enable
2015-01-27 clock add
2015-01-27 +empty logtasks
2015-01-27 Log
    +logtask
    -Openlog.c
    +binary logging
2015-01-27 Updated mpc and system matrices
2015-01-27 Updated system matrices
2015-01-27 Changes due to update of mpc
2015-01-28 + Data logging task
    Bug fixes on STM ... misused memccpy
2015-01-28 MPC IS WORKING
2015-01-28 + Angles from FlightCTRL
2015-01-28 Konečně to funguje!
2015-01-29 log prepeared
2015-01-30 +time set command (unix time)
2015-01-30 Updated CMatricLib
2015-01-30 Controllers on change
2015-01-30 Towards a better code (do not use)
2015-01-31 controller automatic start init
2015-01-31 Setpoint from xMega
2015-01-31 controllers.c clean
2015-02-01 time int fix
2015-02-02 + Estimating of disturbances
2015-02-05 + Identifikace Honza Chudoba
2015-02-05 Bug fix in identification
2015-02-06 Sume rollbacks, STILL UNTESTED
2015-02-06 MPC refactored, UNTESTED
2015-02-07 Refractored MPC and Kalman should fly
2015-02-07 trajectory change
2015-02-08 Various bug fixes
    + Error acceleration tuned
2015-02-09 + Altitude identification
    + Action penalization enlarged in MPC
2015-02-10 Critical bug fix in comm
2015-02-10 Removed redundant matrices
2015-02-10 OpenLog hex corrected
2015-02-11 + Initial conditions for kalman
2015-02-11 Blob fix
2015-02-11 Landing Debug
2015-02-11 + altitude controller finetuned
2015-02-13 MPC parameters fine-tuned
2015-02-14 Identification tweaks
2015-02-14 + Minor changes
2015-02-17 + trajectory tracking on xMega
2015-02-17 +STM
2015-02-17 XBee comm upgrade
2015-02-17 Switch on 2x faster incomming ppm
2015-02-18 + BugFix with floats and context switch
    + Slightly higher Q
    + Fine tuning circle trajectory following
2015-02-22 After the experiment
2015-02-22 + Matlab generator videa
2015-02-23 speed pos acceleration struct
2015-03-03 + Mikrokopter identification
2015-03-03 Some figure fixes
2015-03-04 + Plotting changes
2015-03-09 Fine tuning
2015-03-09 Color change
2015-03-10 protocol clear
2015-03-22 Label changes
2015-03-23 Rpi "works" with tricopter
2015-03-30 setfollower
2015-03-31 position set
2015-03-31 Trajectory set
2015-03-31 -lock on blob
2015-03-31 +positionSlave
2015-04-01 trajectory fix -speed setpoint
2015-04-14 +MPC
2015-04-15 +Kalman telemetry +MPC trajectory
2015-04-16 trajectory report debug
2015-04-23 position slave send debug
2015-04-25 Plots updated
2015-04-26 Identifikace 250
2015-05-03 get status change; tel to coord packet struct change
2015-05-03 tel to coord packet debug
2015-05-05 log debug
2015-05-12 + iden 250
2015-06-18 More robust altitude controller
2015-06-18 + plot videa velka formace
2015-06-19 - PID cont
2015-06-19 -pitch -roll
2015-06-20 GUI final
2015-07-10 MPC Landing
2015-07-28 Small changes
2015-08-12 log task num
2015-08-12 +4slave address
2015-08-26 Towards MultiCon
2015-08-27 Multicon receiver is working
2015-09-01 Tricopter reidentified
    + small delay to failsave
2015-09-23 Englification
2015-10-06 removed additional matrices
2016-01-05 Working on magnetometer
    + Raspberry in its own file
2016-01-13 Update navodu
2016-01-13 Update manualu
2016-01-25 XBEE in API works
2016-01-25 brap
2016-01-25 Before first logging
2016-01-27 + battery discharging data log
2016-02-04 Předpřipraveno pro vývoj
2016-02-09 Few changes
2016-02-10 pokusy s posíláním zpráv
    napsána komunikační fronta z commTasku do mainTasku. V mainTasku
    implementovány základní funkce algoritmu, jen pro ověření funkčnosti.
2016-02-15 Kalman dodělaný
    Měl by fungovat, logovací task loguje výstup kalmanu, zpětná vazba ještě
    není.
2016-02-18 Zaveden Feedback
    zavedena zpětná vazba, opraven bug kdy kalman s různým počtem vstupů a
    senzorů vracel vždy nulový stav
2016-02-19 snad už funkční
2016-02-22 Hotfix 1
    Opraveny drobné chyby při kompilaci
2016-03-02 Added error state
    improved kalman fit
2016-03-03 Uploadnutá identifikace
    brap
2016-03-07 Fixed bug with Kalman in STM
2016-03-11 Startér
    zapíná kalman na začátku letu
2016-03-11 logovani2
    přidány další proměnné
2016-03-13 Nový model
    Nahozen nový model kde chybový stav zcela nahrazuje konstanty.
2016-03-17 První test ZV
    testována zpětná vazba, zatím pouze formou logování
2016-03-21 ¨navrh lqr regulatoru
    brap
2016-03-21 Opraveno pořadí stavů
    příprava pro stavovou ZV
2016-04-15 Many changes
2016-04-15 Bug fixes
2016-04-15 UART baudrates updates up to 400kbps
2016-04-16 Polishing the code
2016-04-18 přidány logy
    nalogován výstup MPC s kvadrokoptérou v ruce
2016-04-21 Code polishing
2016-04-25 Přidány další logy
    vše se zdá být v pořádku
2016-04-28 Few changes regarding XBEE, new LOG from experiment
2016-04-29 Staré edity
    zapomněl jsem je commitnout když jsem je udělal
2016-05-05 Nastavitelný výškový setpoint
    Přidáno nastavení setpointu výškové regulace na kanál AUX3, výšky
    nastaveny na 1, 1,5 a 2m.
2016-09-21 Added support for gumstix

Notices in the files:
parts and their libraries:
Copyright (C) PaJa 2011
